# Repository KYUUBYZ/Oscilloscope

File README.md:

# Oscilloscope

<!--START_SECTION:BOM-TABLE-->
| Item | Qty | Supplier | Cost/item | Total Cost | link |
| --- | --- | --- | --- | --- | --- |
| 47R | 1 | Unikeyic | $0.00 | $0.00 | [Link](https://www.unikeyic.com/products/surface-mount-resistors/frc0805f47r0ts/982873643.html?sku=1003001039920123) |
| 1K | 1 | Unikeyic | $0.00 | $0.00 | [Link](https://www.unikeyic.com/products/surface-mount-resistors/wr08x102-jtl/33997435.html?sku=1003001013110885) |
| 1k | 1 | Unikeyic | $0.00 | $0.00 | [Link](https://www.unikeyic.com/products/surface-mount-resistors/wr08x102-jtl/33997435.html?sku=1003001013110885) |
| 470k | 1 | Unikeyic | $0.01 | $0.01 | [Link](https://www.unikeyic.com/products/surface-mount-resistors/ac0805jr-07470kl/32881456.html?sku=1003001023882967) |
| 0R | 1 | Unikeyic | $0.01 | $0.01 | [Link](https://www.unikeyic.com/products/surface-mount-resistors/rtt050000ftp/30082103.html?sku=1003001013772933) |
| 100nF | 3 | Unikeyic | $0.01 | $0.03 | [Link](https://www.unikeyic.com/products/ceramic-capacitors/0805b104k250ct/6132896.html?sku=1003001022740982) |
| BAT54S | 1 | Unikeyic | $0.01 | $0.01 | [Link](https://www.unikeyic.com/products/schottky-diodes/bat54s/1005561198.html?sku=1003001034622180) |
| 1nF | 1 | Unikeyic | $0.01 | $0.01 | [Link](https://www.unikeyic.com/products/ceramic-capacitors/cc0805krx7rabb102/7614988.html?sku=1003001445182757) |
| 2.2pF | 2 | Unikeyic | $0.01 | $0.02 | [Link](https://www.unikeyic.com/products/ceramic-capacitors/cc0805crnpo9bn2r2/20735051.html?sku=1003001010741217) |
| SN74LVC1G125DCK | 1 | Unikeyic | $0.02 | $0.02 | [Link](https://www.unikeyic.com/products/logic-buffers-and-line-drivers/sn74lvc1g125dckr/1014674710.html?sku=1003001043007378) |
| 10nF | 1 | Unikeyic | $0.02 | $0.02 | [Link](https://www.unikeyic.com/products/ceramic-capacitors/ac0805kkx7rybb103/17516205.html?sku=1003001016410454) |
| 10pF 1% | 1 | Unikeyic | $0.02 | $0.02 | [Link](https://www.unikeyic.com/products/ceramic-capacitors/cc0805frnpo9bn100/7443730.html?sku=1003001011768162) |
| 100nF | 1 | Unikeyic | $0.02 | $0.02 | [Link](https://www.unikeyic.com/products/ceramic-capacitors/0805b104k250ct/6132896.html?sku=1003001022740982) |
| 10uM | 1 | Unikeyic | $0.03 | $0.03 | [Link](https://www.unikeyic.com/products/chip-inductor/mlf2012e100kt000/24229775.html?sku=1003001445897236) |
| 1uF | 3 | Unikeyic | $0.03 | $0.09 | [Link](https://www.unikeyic.com/products/ceramic-capacitors/c0805c105j8nac7800/7749019.html?sku=1003001430122656) |
| 1N5819 | 1 | Unikeyic | $0.03 | $0.03 | [Link](https://www.unikeyic.com/products/other-diodes/1n5819/25738005.html?sku=1003001013772519) |
| 22pF | 1 | Unikeyic | $0.03 | $0.03 | [Link](https://www.unikeyic.com/products/ceramic-capacitors/cc0805frnpo9bn220/5559781.html?sku=100300109292543) |
| 100pF | 1 | Unikeyic | $0.03 | $0.03 | [Link](https://www.unikeyic.com/products/ceramic-capacitors/gcm2165c2a101ja16d/20357284.html?sku=1003001021093361) |
| 27pF | 1 | Unikeyic | $0.03 | $0.03 | [Link](https://www.unikeyic.com/products/ceramic-capacitors/cc0805frnpo9bn270/21734348.html?sku=1003001020073576) |
| 499k 0.1% | 2 | Unikeyic | $0.04 | $0.08 | [Link](https://www.unikeyic.com/products/surface-mount-resistors/tc0525b4993t5g/688229128.html?sku=1003001046152118) |
| 22uF | 2 | Unikeyic | $0.06 | $0.12 | [Link](https://www.unikeyic.com/products/ceramic-capacitors/tcc0805x5r226m160ft/21907184.html?sku=1003001026937046) |
| 10uF | 1 | Unikeyic | $0.07 | $0.07 | [Link](https://www.unikeyic.com/products/ceramic-capacitors/0805x106k160ct/17200396.html?sku=1003001013112822) |
| 10k 0.1% | 4 | Unikeyic | $0.07 | $0.28 | [Link](https://www.unikeyic.com/products/surface-mount-resistors/ptfr0805b10k0p9/7247758.html?sku=1003001017271404) |
| 50R | 1 | Unikeyic | $0.07 | $0.07 | [Link](https://www.unikeyic.com/products/surface-mount-resistors/ar05dtbw0500/683416237.html?sku=1003001018009187) |
| MT3608 | 1 | Unikeyic | $0.10 | $0.10 | [Link](https://www.unikeyic.com/products/other-ics/mt3608/34222425.html?sku=1003001013612482) |
| OPA2365AID | 1 | Unikeyic | $0.43 | $0.43 | [Link](https://www.unikeyic.com/products/op-amplifiers/opa2365aidr/33377575.html?sku=1003001434234027) |
| REF5050AD | 1 | Unikeyic | $0.72 | $0.72 | [Link](https://www.unikeyic.com/products/voltage-references-ics/ref5050aidgkr/34018870.html?sku=1003001031469596) |
| OPA735AIDBVR | 1 | 0 | $2.00 | $2.00 | [Link](https://73) |
| ADS7883SBDBVR | 1 | Unikeyic | $3.66 | $3.66 | [Link](https://www.unikeyic.com/products/adcs/ads7883sdbvr/33187951.html?sku=1003001027332150) |
| RP2040-Zero | 1 | AliExpress | $3.90 | $3.90 | [Link](https://www.aliexpress.com/item/1005010768723373.html?spm=a2g0o.cart.0.0.4b8438daNiUA5Y&mp=1&pdp_npi=6%40dis%21USD%21USD%203.90%21USD%203.90%21%21USD%203.90%21%21%21%400b88486a17935424509128878e0ea7%2112000056461341594%21ct%21IT%216215000935%21%211%210%21) |
| MSP2402 | 1 | Aliexpress | $4.80 | $4.80 | [Link](https://it.aliexpress.com/item/1005006173440437.html?spm=a2g0o.cart.0.0.4b8438daNiUA5Y&mp=1&pdp_npi=6%40dis%21USD%21USD%208.57%21USD%204.80%21%21USD%204.80%21%21%21%400b88486a17935424485818824e0ea7%2112000036216232691%21ct%21IT%216215000935%21%211%210%21&gatewayAdapt=glo2ita) |
| BNC | 1 | AliExpress | $6.33 | $6.33 | [Link](https://www.aliexpress.com/item/1005003950007418.html?spm=a2g0o.cart.0.0.4b8438daNiUA5Y&mp=1&pdp_npi=6%40dis%21USD%21USD%206.48%21USD%206.33%21%21USD%206.33%21%21%21%400b88486a17935424485818824e0ea7%2112000027542547180%21ct%21IT%216215000935%21%211%210%21) |
| Estimated total shipping | 1 |  |  | $8.00 |  |
<!--END_SECTION:BOM-TABLE-->

This is my DIY oscilloscope, it's not a super advanced one, but you can measure PWM signals with this, in my case i work a lot with servos so it's an useful project, lemme know what you think about it.

# How it works:

My oscilloscope uses an RP2040-ZERO as microcontroller, i use it a lot, it's cheap, it has a lot of GPio pins and its small. Via usb-c to a power source, it transmit its 5V output to the MT3608 module where it become 7V, then these 7V go to the REF5050, where they become a really stable 5V to be used as reference for the ADS7883 (the OPA735's purpose is to get buffed).

The BNC gets its data and they get sent to the Vbias and +IN_A definer (part of the opa2365 module) and they become readeble data for the ADS7883's VIN where they become a 12 bits sequence and become digital , so, readable for the RP2040-ZERO's chip

# Up-view:

# Front-view:

# PCB-view:

# Schematic-view:

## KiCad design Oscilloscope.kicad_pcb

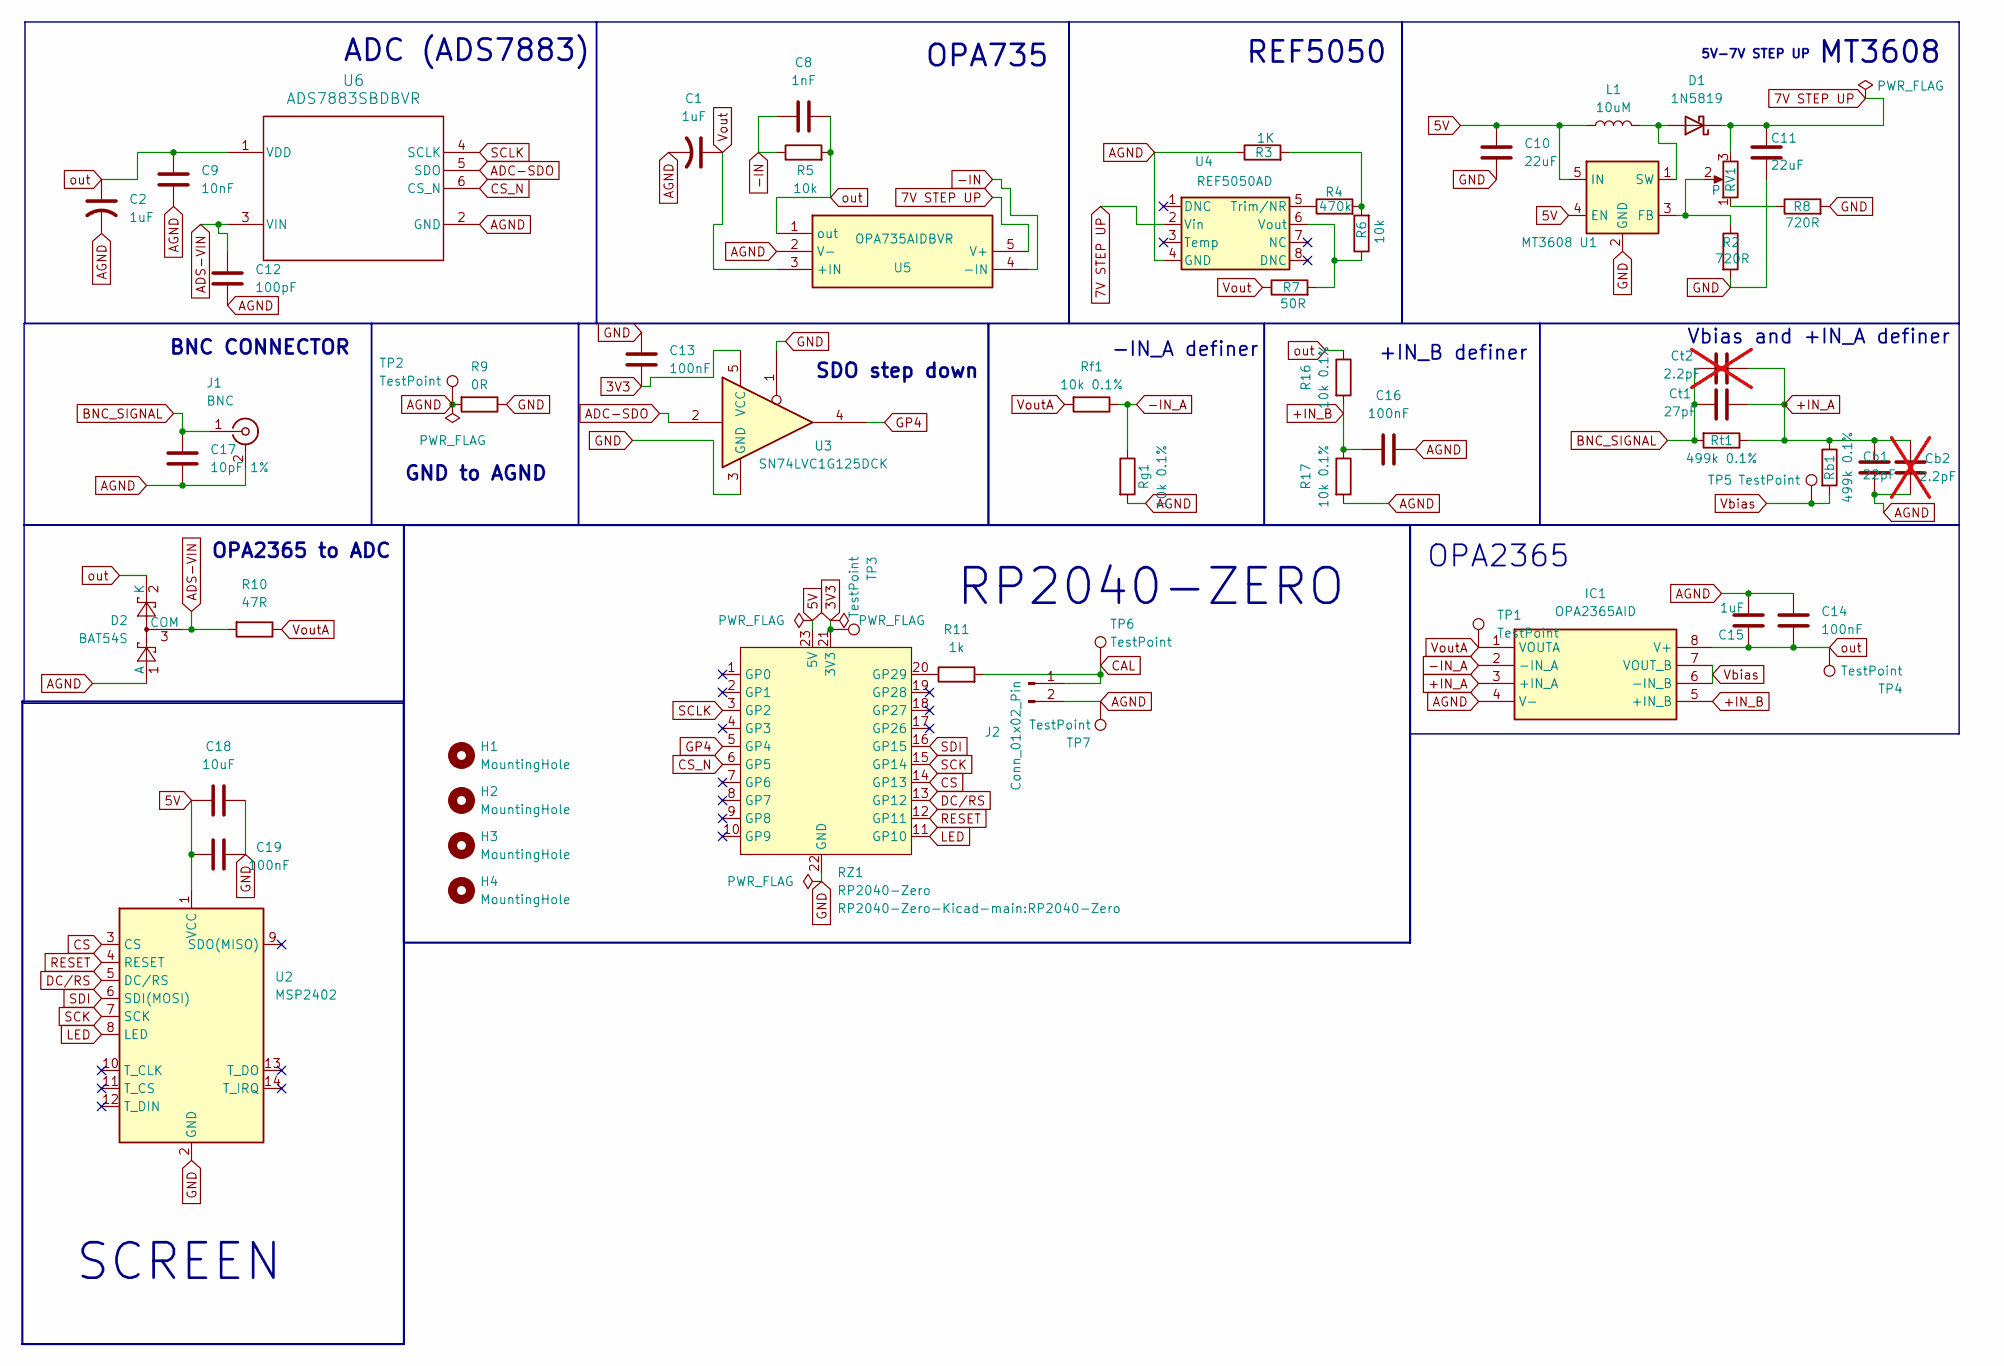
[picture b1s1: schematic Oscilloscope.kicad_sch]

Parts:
C1, C2, C15: 1uF; C_0805_2012Metric_Pad1.18x1.45mm_HandSolder
C8: 1nF; C_0805_2012Metric_Pad1.18x1.45mm_HandSolder
C9: 10nF; C_0805_2012Metric_Pad1.18x1.45mm_HandSolder
C10, C11: 22uF; C_0805_2012Metric_Pad1.18x1.45mm_HandSolder
C12: 100pF; C_0805_2012Metric_Pad1.18x1.45mm_HandSolder
C13, C14, C16, C19: 100nF; C_0805_2012Metric_Pad1.18x1.45mm_HandSolder
C17: 10pF 1%; C_0805_2012Metric_Pad1.18x1.45mm_HandSolder
C18: 10uF; C_0805_2012Metric_Pad1.18x1.45mm_HandSolder
Cb1: 22pF; C_0805_2012Metric_Pad1.18x1.45mm_HandSolder
Cb2: 2.2pF; C_0201_0603Metric_Pad0.64x0.40mm_HandSolder; not fitted
Ct1: 27pF; C_0805_2012Metric_Pad1.18x1.45mm_HandSolder
Ct2: 2.2pF; C_0201_0603Metric_Pad0.64x0.40mm_HandSolder; not fitted
D1: 1N5819; D_DO-41_SOD81_P10.16mm_Horizontal
D2: BAT54S; SOT-23_Handsoldering
H1, H2, H3, H4: MountingHole; MountingHole_2.2mm_M2
IC1: OPA2365AID; SOIC127P600X175-8N; Manufacturer_Part_Number OPA2365AID; Mouser Part Number 595-OPA2365AID
J1: BNC; BNC_Amphenol_B6252HB-NPP3G-50_Horizontal
J2: Conn_01x02_Pin; PinHeader_1x02_P2.54mm_Vertical
L1: 10uM; L_0805_2012Metric_Pad1.05x1.20mm_HandSolder
R2, R8: 720R; R_0805_2012Metric_Pad1.20x1.40mm_HandSolder
R3: 1K; R_0805_2012Metric_Pad1.20x1.40mm_HandSolder
R4: 470k; R_0805_2012Metric_Pad1.20x1.40mm_HandSolder
R5, R6: 10k; R_0805_2012Metric_Pad1.20x1.40mm_HandSolder
R7: 50R; R_0805_2012Metric_Pad1.20x1.40mm_HandSolder
R9: 0R; R_0805_2012Metric_Pad1.20x1.40mm_HandSolder
R10: 47R; R_0805_2012Metric_Pad1.20x1.40mm_HandSolder
R11: 1k; R_0805_2012Metric_Pad1.20x1.40mm_HandSolder
R16, R17: 10k 0.1%; R_0805_2012Metric_Pad1.20x1.40mm_HandSolder
RV1: P; Potentiometer_Bourns_3296W_Vertical
RZ1: RP2040-Zero
Rb1: 499k 0.1%; R_0805_2012Metric_Pad1.20x1.40mm_HandSolder
Rf1: 10k 0.1%; R_0805_2012Metric_Pad1.20x1.40mm_HandSolder
Rg1: 10k 0.1%; R_0805_2012Metric_Pad1.20x1.40mm_HandSolder
Rt1: 499k 0.1%; R_0805_2012Metric_Pad1.20x1.40mm_HandSolder
TP1, TP2, TP3, TP4, TP5, TP6, TP7: TestPoint; TestPoint_Pad_1.5x1.5mm
U1: MT3608; SOT-23-6_Handsoldering
U2: MSP2402; MSP2402_Header_1x14_P2.54mm_Vertical
U3: SN74LVC1G125DCK; Texas_R-PDSO-G5_DCK-5
U4: REF5050AD; SOIC-8_3.9x4.9mm_P1.27mm
U5: OPA735AIDBVR; opa735aidbvr
U6: ADS7883SBDBVR; DBV0006A_N

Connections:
3V3: C13.1, RZ1.21 (3V3), TP3.1 (1_1), U3.5 (VCC)
5V: C10.2, C18.2, C19.1, L1.1, RZ1.23 (5V), U1.4 (EN), U1.5 (IN), U2.1 (VCC)
7V STEP UP: C11.1, D1.1 (K), RV1.3, U4.2 (Vin), U5.5 (V+)
+IN_A: Cb1.2, Cb2.1, Ct1.1, Ct2.2, IC1.3 (+IN_A), Rb1.1, Rt1.1
+IN_B: C16.2, IC1.5 (+IN_B), R16.2, R17.1
-IN: C8.1, R5.1, U5.4 (-IN)
-IN_A: IC1.2 (-IN_A), Rf1.1, Rg1.1
ADC-SDO: U3.2, U6.5 (SDO)
ADS-VIN: C12.2, D2.3 (COM), R10.2, U6.3 (VIN)
AGND: C1.2, C2.2, C9.1, C12.1, C14.2, C15.2, C16.1, C17.1, Cb1.1, Cb2.2, D2.1 (A), IC1.4 (V-), J1.2 (Ext), J2.2, R3.1, R9.2, R17.2, Rg1.2, TP2.1 (1_1), TP7.1 (1_1), U4.4 (GND), U5.2 (V-), U6.2 (GND)
BNC_SIGNAL: C17.2, Ct1.2, Ct2.1, J1.1 (In), Rt1.2
CAL: J2.1, R11.2, TP6.1 (1_1)
CS: RZ1.14 (GP13), U2.3 (CS)
CS_N: RZ1.6 (GP5), U6.6 (CS_N)
DC/RS: RZ1.13 (GP12), U2.5 (DC/RS)
GND: C10.1, C11.2, C13.2, C18.1, C19.2, R2.2, R8.2, R9.1, RZ1.22 (GND), U1.2 (GND), U2.2 (GND), U3.1, U3.3 (GND)
GP4: RZ1.5 (GP4), U3.4
LED: RZ1.11 (GP10), U2.8 (LED)
unnamed: D1.2 (A), L1.2, U1.1 (SW)
unnamed: R3.2, R4.2, R6.2
unnamed: R8.1, RV1.1
unnamed: R11.1, RZ1.20 (GP29)
unnamed: R2.1, RV1.2, U1.3 (FB)
unnamed: R4.1, U4.5 (Trim/NR)
unnamed: R6.1, R7.2, U4.6 (Vout)
RESET: RZ1.12 (GP11), U2.4 (RESET)
SCK: RZ1.15 (GP14), U2.7 (SCK)
SCLK: RZ1.3 (GP2), U6.4 (SCLK)
SDI: RZ1.16 (GP15), U2.6 (SDI(MOSI))
Vbias: IC1.6 (-IN_B), IC1.7 (VOUT_B), Rb1.2, TP5.1 (1_1)
Vout: C1.1, R7.1, U5.3 (+IN)
VoutA: IC1.1 (VOUTA), R10.1, Rf1.2, TP1.1 (1_1)
out: C2.1, C8.2, C9.2, C14.1, C15.1, D2.2 (K), IC1.8 (V+), R5.2, R16.1, TP4.1 (1_1), U5.1 (out), U6.1 (VDD)

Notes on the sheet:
5V-7V STEP UP
MT3608
ADC (ADS7883)
+IN_B definer
SCREEN
REF5050
OPA2365
BNC CONNECTOR
RP2040-ZERO
SDO step down
OPA2365 to ADC
-IN_A definer
GND to AGND
OPA735
Vbias and +IN_A definer

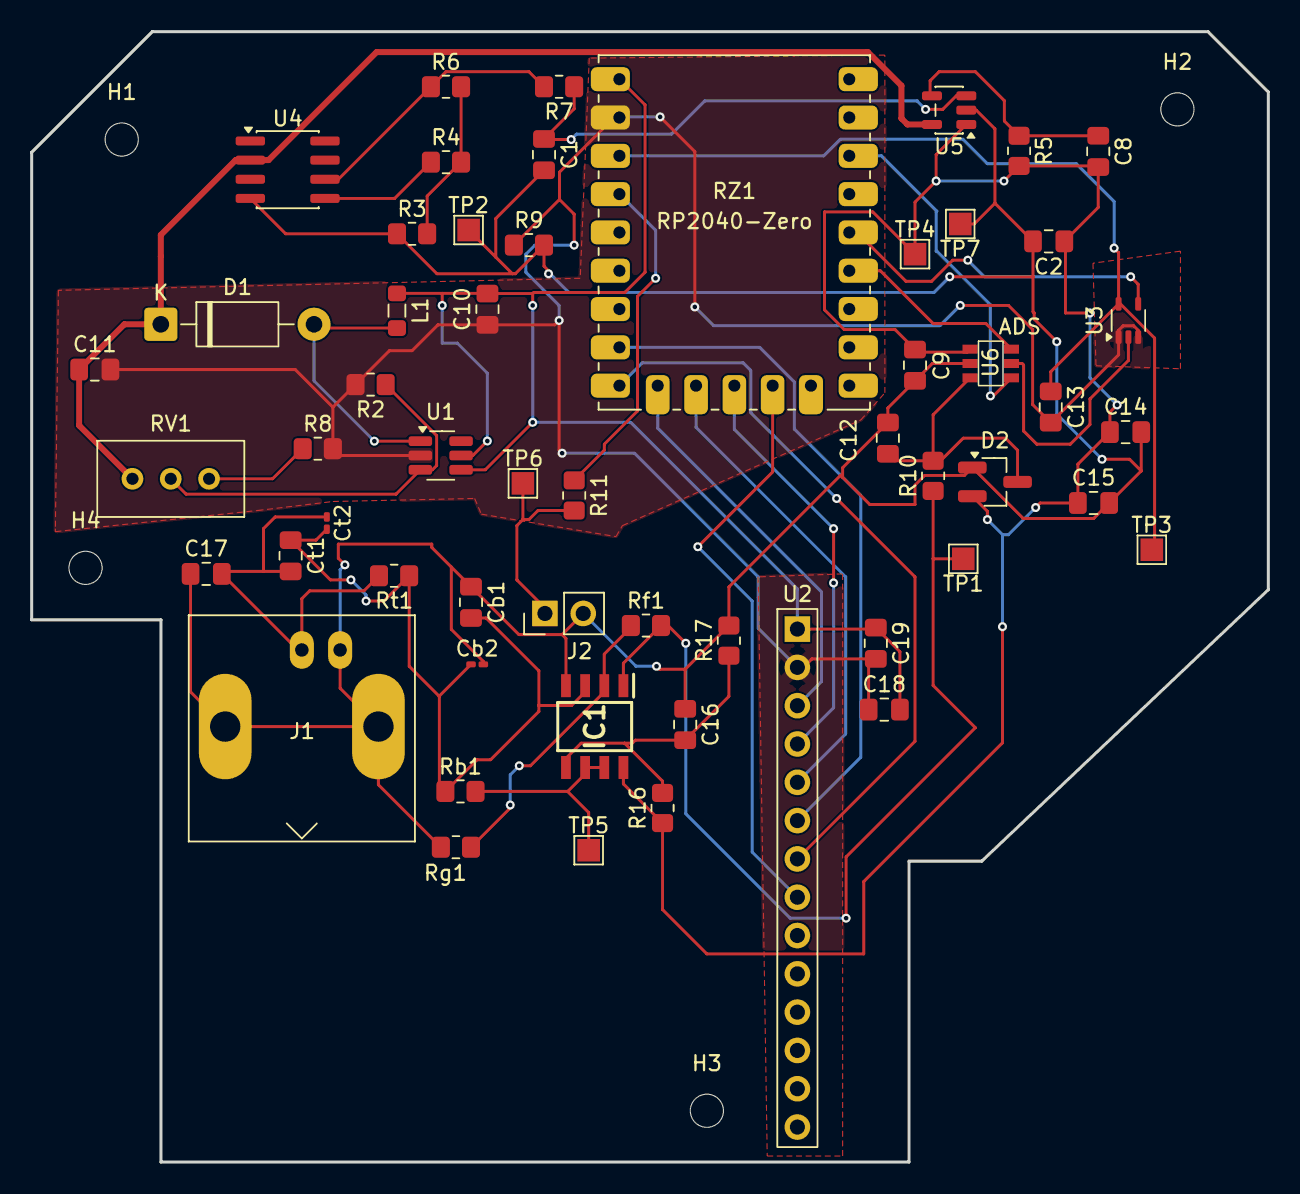
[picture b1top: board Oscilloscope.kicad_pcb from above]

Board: 2 copper layers, 82.0 x 75.0 mm, 59 parts (0 on the bottom side), 33 nets.

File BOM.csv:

Item,Qty,Supplier,Cost/item,Total Cost,link
47R,1,Unikeyic,$0.00,$0.00,https://www.unikeyic.com/products/surface-mount-resistors/fr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
1K,1,Unikeyic,$0.00,$0.00,https://www.unikeyic.com/products/surface-mount-resistors/wr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
1k,1,Unikeyic,$0.00,$0.00,https://www.unikeyic.com/products/surface-mount-resistors/wr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
470k,1,Unikeyic,$0.01,$0.01,https://www.unikeyic.com/products/surface-mount-resistors/ac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
0R,1,Unikeyic,$0.01,$0.01,https://www.unikeyic.com/products/surface-mount-resistors/rt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
100nF,3,Unikeyic,$0.01,$0.03,https://www.unikeyic.com/products/ceramic-capacitors/0805b10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
BAT54S,1,Unikeyic,$0.01,$0.01,https://www.unikeyic.com/products/schottky-diodes/bat54s/100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
1nF,1,Unikeyic,$0.01,$0.01,https://www.unikeyic.com/products/ceramic-capacitors/cc0805k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
2.2pF,2,Unikeyic,$0.01,$0.02,https://www.unikeyic.com/products/ceramic-capacitors/cc0805c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
SN74LVC1G125DCK,1,Unikeyic,$0.02,$0.02,https://www.unikeyic.com/products/logic-buffers-and-line-dri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
10nF,1,Unikeyic,$0.02,$0.02,https://www.unikeyic.com/products/ceramic-capacitors/ac0805k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
10pF 1%,1,Unikeyic,$0.02,$0.02,https://www.unikeyic.com/products/ceramic-capacitors/cc0805f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
100nF,1,Unikeyic,$0.02,$0.02,https://www.unikeyic.com/products/ceramic-capacitors/0805b10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
10uM,1,Unikeyic,$0.03,$0.03,https://www.unikeyic.com/products/chip-inductor/mlf2012e100k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
1uF,3,Unikeyic,$0.03,$0.09,https://www.unikeyic.com/products/ceramic-capacitors/c0805c1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
1N5819,1,Unikeyic,$0.03,$0.03,https://www.unikeyic.com/products/other-diodes/1n5819/257380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
22pF,1,Unikeyic,$0.03,$0.03,https://www.unikeyic.com/products/ceramic-capacitors/cc0805f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
100pF,1,Unikeyic,$0.03,$0.03,https://www.unikeyic.com/products/ceramic-capacitors/gcm2165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
27pF,1,Unikeyic,$0.03,$0.03,https://www.unikeyic.com/products/ceramic-capacitors/cc0805f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
499k 0.1%,2,Unikeyic,$0.04,$0.08,https://www.unikeyic.com/products/surface-mount-resistors/tc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
22uF,2,Unikeyic,$0.06,$0.12,https://www.unikeyic.com/products/ceramic-capacitors/tcc0805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
10uF,1,Unikeyic,$0.07,$0.07,https://www.unikeyic.com/products/ceramic-capacitors/0805x10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
10k 0.1%,4,Unikeyic,$0.07,$0.28,https://www.unikeyic.com/products/surface-mount-resistors/pt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
50R,1,Unikeyic,$0.07,$0.07,https://www.unikeyic.com/products/balun/hhm1517/10710165.htm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
MT3608,1,Unikeyic,$0.10,$0.10,https://www.unikeyic.com/products/other-ics/mt3608/34222425.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
OPA2365AID,1,Unikeyic,$0.43,$0.43,https://www.unikeyic.com/products/op-amplifiers/opa2365aidr/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
REF5050AD,1,Unikeyic,$0.72,$0.72,https://www.unikeyic.com/products/voltage-references-ics/ref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
OPA735AIDBVR,1,0,$2.00,$2.00,https://73
ADS7883SBDBVR,1,Unikeyic,$3.66,$3.66,https://www.unikeyic.com/products/adcs/ads7883sdbvr/33187951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
RP2040-Zero,1,AliExpress,$3.90,$3.90,https://www.aliexpress.com/item/1005010768723373.html?spm=a2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
MSP2402,1,Aliexpress,$4.80,$4.80,https://it.aliexpress.com/item/1005006173440437.html?spm=a2g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
BNC,1,AliExpress,$6.33,$6.33,https://www.aliexpress.com/item/1005003950007418.html?spm=a2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
Estimated total shipping,1,,$0.00,$0.00,
Estimated total shipping,1,,,$0.00,
